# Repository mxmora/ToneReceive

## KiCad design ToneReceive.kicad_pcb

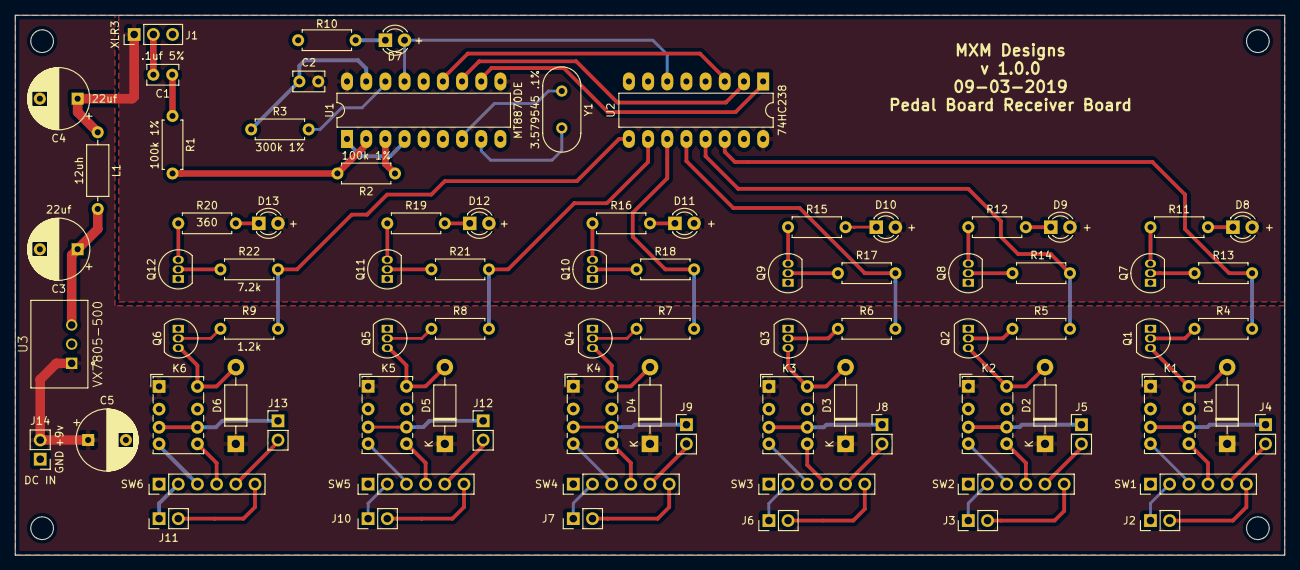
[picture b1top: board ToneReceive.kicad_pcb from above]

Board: 2 copper layers, 168.1 x 71.5 mm, 87 parts (0 on the bottom side), 90 nets.

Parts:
C1: .1uf 5%; C_Rect_L4.0mm_W2.5mm_P2.50mm
C2: 100nf 5%; C_Rect_L4.0mm_W2.5mm_P2.50mm
C3, C4: 22uf; CP_Radial_D8.0mm_P5.00mm
C5: 10uf; CP_Radial_D8.0mm_P5.00mm
D1, D2, D3, D4, D5, D6: 1N4001; D_DO-41_SOD81_P10.16mm_Horizontal
D7, D8, D9, D10, D11, D12, D13: LED; LED_D3.0mm
H1, H2, H3, H4: MountingHole; MountingHole_3mm
J1: XLR3; PinHeader_1x03_P2.54mm_Vertical
J2, J3, J4, J5, J6, J7, J8, J9, J10, J11, J12, J13: 1/4" Jack; PinHeader_1x02_P2.54mm_Vertical
J14: 9v DC in; PinHeader_1x02_P2.54mm_Vertical
K1, K2, K3, K4, K5, K6: G6K-2; Relay_DPDT_Omron_G6K-2P-Y
L1: 12uh; L_Axial_L6.6mm_D2.7mm_P10.16mm_Horizontal_Vishay_IM-2
Q1, Q2, Q3, Q4, Q5, Q6, Q7, Q8, Q9, Q10, Q11, Q12: PN2222A; TO-92_Inline
R1, R2: 100k 1%; R_Axial_DIN0207_L6.3mm_D2.5mm_P7.62mm_Horizontal
R3: 300k 1%; R_Axial_DIN0207_L6.3mm_D2.5mm_P7.62mm_Horizontal
R4, R5, R6, R7, R8, R9: 1.2k; R_Axial_DIN0207_L6.3mm_D2.5mm_P7.62mm_Horizontal
R10: 1k; R_Axial_DIN0207_L6.3mm_D2.5mm_P7.62mm_Horizontal
R11, R12, R15, R16, R19, R20: 360; R_Axial_DIN0207_L6.3mm_D2.5mm_P7.62mm_Horizontal
R13, R14, R17, R18, R21, R22: 7.2k; R_Axial_DIN0207_L6.3mm_D2.5mm_P7.62mm_Horizontal
SW1, SW2, SW3, SW4, SW5, SW6: SW_DPDT_x2; PinHeader_1x06_P2.54mm_Vertical
U1: MT8870DE; DIP-18_W7.62mm_LongPads
U2: 74HC238; DIP-16_W7.62mm_LongPads
U3: VX7805-500; VX78012-500_VX7805-500
Y1: 3.579545 .1%; Crystal_HC18-U_Vertical

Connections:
+5V: C2.2, C4.1, D8.2, D9.2, D10.2, D11.2, D12.2, D13.2, J1.1, L1.1, U1.5, U1.10, U1.18, U2.16
+9V: C5.1, D1.1, D2.1, D3.1, D4.1, D5.1, D6.1, J14.2, K1.1, K2.1, K3.1, K4.1, K5.1, K6.1, U3.1
A0: U1.11, U2.1
A1: U1.12, U2.2
A2: U1.13, U2.3
BTN1: R4.2, R13.2, U2.14
BTN2: R5.2, R14.2, U2.13
BTN3: R6.2, R17.2, U2.12
BTN4: R7.2, R18.2, U2.11
BTN5: R8.2, R21.2, U2.10
BTN6: R9.2, R22.2, U2.9
GND: C3.2, C4.2, C5.2, J1.3, J14.1, Q1.1, Q2.1, Q3.1, Q4.1, Q5.1, Q6.1, Q7.1, Q8.1, Q9.1, Q10.1, Q11.1, Q12.1, R10.1, U1.9, U2.4, U2.5, U2.8, U3.2
unnamed: C1.1, R1.1
unnamed: C1.2, J1.2
unnamed: C2.1, R3.1, U1.17
unnamed: C3.1, L1.2, U3.3
unnamed: D1.2, K1.8, Q1.3
unnamed: D2.2, K2.8, Q2.3
unnamed: D3.2, K3.8, Q3.3
unnamed: D4.2, K4.8, Q4.3
unnamed: D5.2, K5.8, Q5.3
unnamed: D6.2, K6.8, Q6.3
unnamed: D7.1, R10.2
unnamed: D7.2, U1.15, U2.6
unnamed: D8.1, R11.2
unnamed: D9.1, R12.2
unnamed: D10.1, R15.2
unnamed: D11.1, R16.2
unnamed: D12.1, R19.2
unnamed: D13.1, R20.2
unnamed: J2.1, SW1.2
unnamed: J2.2, SW1.6
unnamed: J3.1, SW2.2
unnamed: J3.2, SW2.6
unnamed: J4.1, K1.3, K1.6
unnamed: J4.2, SW1.5
unnamed: J5.1, K2.3, K2.6
unnamed: J5.2, SW2.5
unnamed: J6.1, SW3.2
unnamed: J6.2, SW3.6
unnamed: J7.1, SW4.2
unnamed: J7.2, SW4.6
unnamed: J8.1, K3.3, K3.6
unnamed: J8.2, SW3.5
unnamed: J9.1, K4.3, K4.6
unnamed: J9.2, SW4.5
unnamed: J10.1, SW5.2
unnamed: J10.2, SW5.6
unnamed: J11.1, SW6.2
unnamed: J11.2, SW6.6
unnamed: J12.1, K5.3, K5.6
unnamed: J12.2, SW5.5
unnamed: J13.1, K6.3, K6.6
unnamed: J13.2, SW6.5
unnamed: K1.4, SW1.3
unnamed: K1.5, SW1.4
unnamed: K2.4, SW2.3
unnamed: K2.5, SW2.4
unnamed: K3.4, SW3.3
unnamed: K3.5, SW3.4
unnamed: K4.4, SW4.3
unnamed: K4.5, SW4.4
unnamed: K5.4, SW5.3
unnamed: K5.5, SW5.4
unnamed: K6.4, SW6.3
unnamed: K6.5, SW6.4
unnamed: Q1.2, R4.1
unnamed: Q2.2, R5.1
unnamed: Q3.2, R6.1
unnamed: Q4.2, R7.1
unnamed: Q5.2, R8.1
unnamed: Q6.2, R9.1
unnamed: Q7.2, R13.1
unnamed: Q7.3, R11.1
unnamed: Q8.2, R14.1
unnamed: Q8.3, R12.1
unnamed: Q9.2, R17.1
unnamed: Q9.3, R15.1
unnamed: Q10.2, R18.1
unnamed: Q10.3, R16.1
unnamed: Q11.2, R21.1
unnamed: Q11.3, R19.1
unnamed: Q12.2, R22.1
unnamed: Q12.3, R20.1
unnamed: R1.2, R2.2, U1.2
unnamed: R2.1, U1.3
unnamed: R3.2, U1.16
unnamed: U1.1, U1.4
unnamed: U1.7, Y1.1
unnamed: U1.8, Y1.2

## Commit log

2019-08-09 first check in
2019-08-30 update from imacpro
2019-09-03 layout PCB
2019-09-04 PCB Layout
